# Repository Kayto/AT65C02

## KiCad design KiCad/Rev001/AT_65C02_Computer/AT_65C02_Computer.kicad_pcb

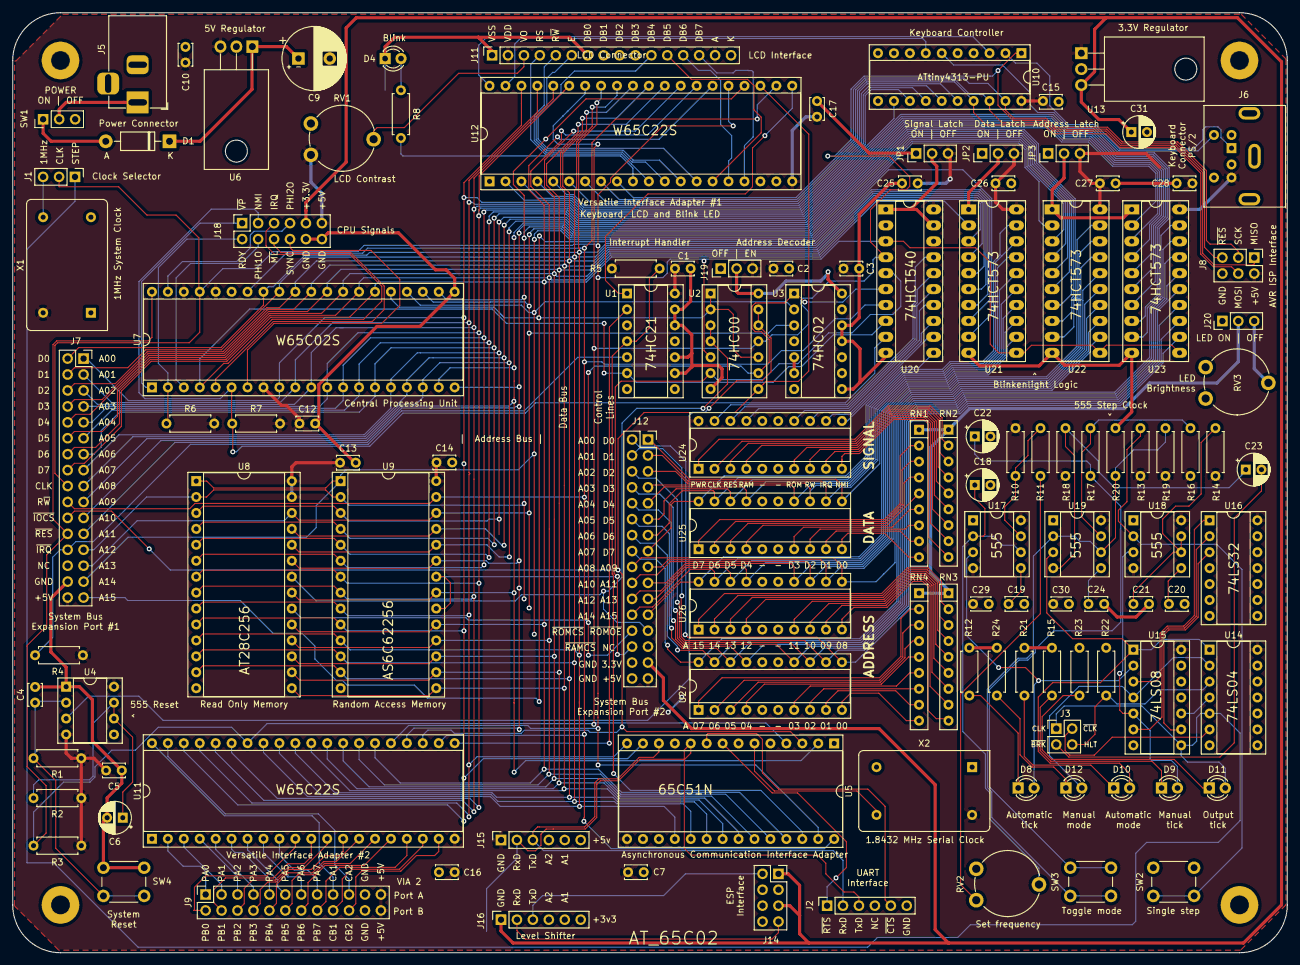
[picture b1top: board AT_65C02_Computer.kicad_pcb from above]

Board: 2 copper layers, 203.2 x 149.9 mm, 122 parts (0 on the bottom side), 200 nets.

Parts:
C1, C2, C3, C4, C5, C7, C10, C12, C13, C14, C15, C16, C17, C19, C20, C21, C24, C25, C26, C27, C28: 0.1uF; C_Disc_D3.4mm_W2.1mm_P2.50mm
C6: 10uF; CP_Radial_D5.0mm_P2.50mm
C9: 1000uF; CP_Radial_D10.0mm_P5.00mm
C18, C22, C23, C31: 1uF; CP_Radial_D5.0mm_P2.50mm
C29: 0.01uF; C_Disc_D3.0mm_W2.0mm_P2.50mm
C30: 0.1uF; C_Disc_D3.0mm_W2.0mm_P2.50mm
D1: 1N5819; D_DO-41_SOD81_P10.16mm_Horizontal
D4: BLINK; LED_D3.0mm
D8: YELLOW_A; LED_D3.0mm
D9: YELLOW_M; LED_D3.0mm
D10: GREEN; LED_D3.0mm
D11: BLUE; LED_D3.0mm
D12: RED; LED_D3.0mm
H1, H2, H3, H4: MountingHole_3mm_Pad
J1: CLK Jumper; PinHeader_1x03_P2.54mm_Vertical
J2: Optional UART Port; PinSocket_1x06_P2.54mm_Vertical
J3: Conn_01x06_Female; PinSocket_2x02_P2.54mm_Vertical
J5: Barrel_Jack-Connector; BarrelJack_Horizontal
J6: Mini-DIN-6; mini_din-6
J7: Expansion port; PinSocket_2x16_P2.54mm_Vertical
J8: AVR-ISP-10; PinHeader_2x03_P2.54mm_Vertical
J9: VIA2PA - VIA2PB; PinSocket_2x12_P2.54mm_Vertical
J11: LCD Connector; PinSocket_1x16_P2.54mm_Vertical
J12: Expansion port #2; PinSocket_2x16_P2.54mm_Vertical
J14: ESP Interface; PinSocket_2x04_P2.54mm_Vertical
J15: Level_Shifter_HV; PinSocket_1x06_P2.54mm_Vertical
J16: Level_Shifter_LV; PinSocket_1x06_P2.54mm_Vertical
J18: CPU Signals; PinSocket_2x06_P2.54mm_Vertical
J19: Address Decoder Enable; PinHeader_1x03_P2.54mm_Vertical
J20: LED SWITCH; PinHeader_1x03_P2.54mm_Vertical
JP1: EN_SIGNAL; PinHeader_1x03_P2.54mm_Vertical
JP2: EN_DATA; PinHeader_1x03_P2.54mm_Vertical
JP3: EN_ADDR; PinHeader_1x03_P2.54mm_Vertical
R1, R14: 1M; R_Axial_DIN0207_L6.3mm_D2.5mm_P7.62mm_Horizontal
R2: 47K; R_Axial_DIN0207_L6.3mm_D2.5mm_P7.62mm_Horizontal
R3: 1k; R_Axial_DIN0207_L6.3mm_D2.5mm_P7.62mm_Horizontal
R4, R5, R6, R7: 4K7; R_Axial_DIN0207_L6.3mm_D2.5mm_P7.62mm_Horizontal
R8: 270; R_Axial_DIN0207_L6.3mm_D2.5mm_P7.62mm_Horizontal
R10, R11, R13, R16, R18, R22: 1K; R_Axial_DIN0207_L6.3mm_D2.5mm_P7.62mm_Horizontal
R12, R15, R21, R23, R24: 220; R_Axial_DIN0207_L6.3mm_D2.5mm_P7.62mm_Horizontal
R17: 100K; R_Axial_DIN0207_L6.3mm_D2.5mm_P7.62mm_Horizontal
R19, R20: 10K; R_Axial_DIN0207_L6.3mm_D2.5mm_P7.62mm_Horizontal
RN1, RN2, RN3, RN4: 330x8; R_Array_SIP9
RV1: 10K; Potentiometer_Piher_PT-10-V10_Vertical
RV2: 1M; Potentiometer_Piher_PT-10-V10_Vertical
RV3: 150k; Potentiometer_Piher_PT-10-V10_Vertical
SW1: SW_SPDT; PinHeader_1x03_P2.54mm_Vertical
SW2: Step; SW_PUSH_6mm
SW3: Mode; SW_PUSH_6mm
SW4: SW_SPDT; SW_PUSH_6mm
U1: 74HC21; DIP-14_W7.62mm_Socket
U2: 74HC00; DIP-14_W7.62mm_Socket
U3: 74HC02; DIP-14_W7.62mm_Socket
U4, U17, U18, U19: NE555; DIP-8_W7.62mm_Socket
U5: 65C51N; DIP-28_W15.24mm_Socket
U6: Regulator_Linear_L7805; TO-220-3_Horizontal_TabDown
U7: 65C02S; DIP-40_W15.24mm_Socket
U8: 28C256; DIP-28_W15.24mm_Socket
U9: 62256; DIP-28_W15.24mm_Socket
U10: ATtiny4313-PU; DIP-20_W7.62mm_Socket
U11, U12: 65C22S; DIP-40_W15.24mm_Socket
U13: L7806; TO-220-3_Horizontal_TabDown
U14: 74LS04; DIP-14_W7.62mm_Socket
U15: 74LS08; DIP-14_W7.62mm_Socket
U16: 74LS32; DIP-14_W7.62mm_Socket
U20: 74HCT540; DIP-20_W7.62mm_Socket_LongPads
U21, U22, U23: 74HCT573; DIP-20_W7.62mm_Socket_LongPads
U24, U25, U26, U27: 10_LED_Array; DIP-20_W7.62mm_Socket
X1: 1MHz; Oscillator_DIP-14
X2: 1.8432MHz; Oscillator_DIP-14

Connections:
+3.3V: C31.1, J12.29, J14.1, J14.5, J16.1, J18.9, U13.3
+5V: C1.1, C2.1, C3.1, C5.1, C7.1, C10.1, C12.1, C13.1, C14.1, C15.1, C16.1, C17.1, C25.1, C26.1, C27.1, C28.1, C29.1, C30.1, J6.4, J7.32, J8.2, J9.23, J9.24, J11.2, J11.15, J12.31, J15.1, J18.11, J19.3, JP1.3, JP2.3, JP3.3, R1.1, R2.1, R3.1, R4.1, R5.1, R6.2, R7.2, R10.1, R13.1, R14.1, R16.1, R18.1, R19.1, RV1.1, U1.14, U4.4, U4.8, U5.15, U6.3, U7.8, U7.36, U7.38, U8.27, U8.28, U9.28, U10.20, U11.20, U12.20, U13.1, U14.14, U15.14, U16.14, U17.4, U17.8, U18.4, U18.8, U19.8, U20.20, U21.20, U22.20, U23.20, U24.20, X1.14, X2.14
/6502 Peripherals/v1pa0: U10.12, U12.2
/6502 Peripherals/v1pa1: U10.13, U12.3
/6502 Peripherals/v1pa2: U10.14, U12.4
/6502 Peripherals/v1pa3: U10.15, U12.5
/6502 Peripherals/v1pa4: U10.16, U12.6
/6502 Peripherals/v1pa5: J8.4, U10.17, U12.7
/6502 Peripherals/v1pa6: J8.1, U10.18, U12.8
/6502 Peripherals/v1pa7: J8.3, U10.19, U12.9
/6502 Peripherals/v1pa8: U10.3, U12.40
/6502 Peripherals/v1pa9: U10.7, U12.39
/6502 Peripherals/v1pb0: R8.1, U12.10
/6502 Peripherals/v1pb1: J11.4, U12.11
/6502 Peripherals/v1pb2: J11.5, U12.12
/6502 Peripherals/v1pb3: J11.6, U12.13
/6502 Peripherals/v1pb4: J11.11, U12.14
/6502 Peripherals/v1pb5: J11.12, U12.15
/6502 Peripherals/v1pb6: J11.13, U12.16
/6502 Peripherals/v1pb7: J11.14, U12.17
/6502 Peripherals/v2pa0: J9.1, U11.2
/6502 Peripherals/v2pa1: J9.3, U11.3
/6502 Peripherals/v2pa2: J9.5, U11.4
/6502 Peripherals/v2pa3: J9.7, U11.5
/6502 Peripherals/v2pa4: J9.9, U11.6
/6502 Peripherals/v2pa5: J9.11, U11.7
/6502 Peripherals/v2pa6: J9.13, U11.8
/6502 Peripherals/v2pa7: J9.15, U11.9
/6502 Peripherals/v2pa8: J9.17, U11.40
/6502 Peripherals/v2pa9: J9.19, U11.39
/6502 Peripherals/v2pb0: J9.2, U11.10
/6502 Peripherals/v2pb1: J9.4, U11.11
/6502 Peripherals/v2pb2: J9.6, U11.12
/6502 Peripherals/v2pb3: J9.8, U11.13
/6502 Peripherals/v2pb4: J9.10, U11.14
/6502 Peripherals/v2pb5: J9.12, U11.15
/6502 Peripherals/v2pb6: J9.14, U11.16
/6502 Peripherals/v2pb7: J9.16, U11.17
/6502 Peripherals/v2pb8: J9.18, U11.18
/6502 Peripherals/v2pb9: J9.20, U11.19
AD_EN: J19.2, U2.14, U3.14
AUTO: D8.2, U15.2, U17.3
CLK: J1.2, J7.18, U2.5, U5.27, U7.37, U11.25, U12.25, U20.3, U21.11, U22.11, U23.11
CLKOUT: J1.3, X1.8
CLKx: D11.2, J1.1, J3.1, U14.5, U15.8
GND: C1.2, C2.2, C3.2, C4.2, C5.2, C6.2, C7.2, C9.2, C10.2, C12.2, C13.2, C14.2, C15.2, C16.2, C17.2, C18.2, C19.2, C20.2, C21.2, C22.2, C24.2, C25.2, C26.2, C27.2, C28.2, C29.2, C30.2, D4.1, J2.6, J5.2, J6.3, J7.30, J8.6, J9.21, J9.22, J11.1, J11.7, J11.8, J11.9, J11.10, J11.16, J12.30, J12.32, J14.8, J15.6, J16.6, J18.10, J18.12, J19.1, JP1.1, JP2.1, JP3.1, R12.2, R15.2, R20.2, R21.2, R22.2, R23.2, R24.2, RV1.3, RV3.3, SW2.1, SW4.1, U1.7, U1.9, U1.10, U1.12, U1.13, U2.7, U3.5, U3.6, U3.7, U3.8, U3.9, U3.11, U3.12, U4.1, U5.1, U5.16, U5.17, U6.2, U7.21, U8.14, U9.14, U10.10, U11.1, U12.1, U13.2, U14.7, U15.7, U16.7, U17.1, U18.1, U19.1, U20.10, U21.10, U22.10, U23.10, X1.7, X2.7
HLT: J3.4, R22.1, U14.3
KBCLK: J6.5, U10.6
KBDAT: J6.1, U10.2
LED_bright: J20.2, RN1.1, RN2.1, RN3.1, RN4.1
MAN: D9.2, U15.5, U18.3
MODE: D10.2, U14.1, U15.1, U19.3
unnamed: C4.1, R1.2, SW4.2, U4.2
unnamed: C6.1, R2.2, U4.6, U4.7
unnamed: C9.1, D1.1, U6.1
unnamed: C18.1, RV2.2, U17.2, U17.6
unnamed: C19.1, U17.5
unnamed: C20.1, U18.5
unnamed: C21.1, R14.2, U18.6, U18.7
unnamed: C22.1, R17.2, SW3.1
unnamed: C23.1, R18.2, U19.4
unnamed: C24.1, U19.5
unnamed: D1.2, SW1.1
unnamed: D4.2, R8.2
unnamed: D8.1, R12.1
unnamed: D9.1, R15.1
unnamed: D10.1, R21.1
unnamed: D11.1, R23.1
unnamed: D12.1, R24.1
unnamed: J5.1, SW1.2
unnamed: J11.3, RV1.2
unnamed: J20.3, RV3.2
unnamed: JP1.2, U20.1, U20.19
unnamed: JP2.2, U21.1
unnamed: JP3.2, U22.1, U23.1
unnamed: R10.2, R11.1, U17.7
unnamed: R11.2, RV2.1
unnamed: R13.2, SW2.2, U18.2
unnamed: R16.2, R17.1, U19.7
unnamed: R19.2, R20.1, SW3.2, U19.2, U19.6
unnamed: RN1.2, U25.1
unnamed: RN1.3, U25.2
unnamed: RN1.4, U25.3
unnamed: RN1.5, U25.4
unnamed: RN1.6, U25.7
unnamed: RN1.7, U25.8
unnamed: RN1.8, U25.9
unnamed: RN1.9, U25.10
unnamed: RN2.2, U24.1
unnamed: RN2.3, U24.2
unnamed: RN2.4, U24.3
unnamed: RN2.5, U24.4
unnamed: RN2.6, U24.7
unnamed: RN2.7, U24.8
unnamed: RN2.8, U24.9
unnamed: RN2.9, U24.10
unnamed: RN3.2, U26.1
unnamed: RN3.3, U26.2
unnamed: RN3.4, U26.3
unnamed: RN3.5, U26.4
unnamed: RN3.6, U26.7
unnamed: RN3.7, U26.8
unnamed: RN3.8, U26.9
unnamed: RN3.9, U26.10
unnamed: RN4.2, U27.1
unnamed: RN4.3, U27.2
unnamed: RN4.4, U27.3
unnamed: RN4.5, U27.4
unnamed: RN4.6, U27.7
unnamed: RN4.7, U27.8
unnamed: RN4.8, U27.9
unnamed: RN4.9, U27.10
unnamed: U2.12, U2.13, U4.3
unnamed: U14.4, U15.10
unnamed: U15.3, U16.1
unnamed: U15.6, U16.2
unnamed: U15.9, U16.3
unnamed: U20.11, U24.11
unnamed: U20.12, U24.12
unnamed: U20.13, U24.13
unnamed: U20.14, U24.14
unnamed: U20.15, U24.17
unnamed: U20.16, U24.18
unnamed: U20.17, U24.19
PHI1O: J18.4, U7.3
PHI2O: J18.7, U7.39
RDY: J18.2, R6.1, U7.2
RS232CLK: U5.6, X2.8
RxD: J2.2, J15.3, U5.12
RxD3: J14.2, J16.3
R~W: J7.20, U5.28, U7.34, U9.27, U11.22, U12.22, U20.7
SYNC: J18.8, U7.7
TxD: J2.3, J15.2, U5.10
TxD3: J14.7, J16.2
a0: J7.1, U5.13, U7.9, U8.10, U9.10, U11.38, U12.38, U23.9
a1: J7.3, U5.14, U7.10, U8.9, U9.9, U11.37, U12.37, U23.8
a2: J7.5, U7.11, U8.8, U9.8, U11.36, U12.36, U23.7
a3: J7.7, U7.12, U8.7, U9.7, U11.35, U12.35, U23.6
a4: J7.9, U7.13, U8.6, U9.6, U23.5
a5: J7.11, U7.14, U8.5, U9.5, U23.4
a6: J7.13, U7.15, U8.4, U9.4, U23.3
a7: J7.15, U7.16, U8.3, U9.3, U23.2
a8: J7.17, U7.17, U8.25, U9.25, U22.9
a9: J7.19, U7.18, U8.24, U9.24, U22.8
a10: J7.21, U5.2, U7.19, U8.21, U9.21, U22.7
a11: J7.23, U7.20, U8.23, U9.23, U11.24, U22.6
a12: J7.25, U7.22, U8.2, U9.2, U12.24, U22.5
a13: J7.27, U3.3, U7.23, U8.26, U9.26, U22.4
a14: J7.29, U3.2, U7.24, U8.1, U9.1, U22.3
a15: J7.31, U2.1, U2.2, U2.10, U7.25, U22.2
ab0: J12.2, U23.12, U27.11
ab1: J12.4, U23.13, U27.12
ab2: J12.6, U23.14, U27.13
ab3: J12.8, U23.15, U27.14
ab4: J12.10, U23.16, U27.17
ab5: J12.12, U23.17, U27.18
ab6: J12.14, U23.18, U27.19
ab7: J12.16, U23.19, U27.20
ab8: J12.18, U22.12, U26.11
ab9: J12.17, U22.13, U26.12
ab10: J12.20, U22.14, U26.13
ab11: J12.19, U22.15, U26.14
ab12: J12.22, U22.16, U26.17
ab13: J12.21, U22.17, U26.18
ab14: J12.24, U22.18, U26.19
ab15: J12.23, U22.19, U26.20
d0: J7.2, U5.18, U7.33, U8.11, U9.11, U11.33, U12.33, U21.9
d1: J7.4, U5.19, U7.32, U8.12, U9.12, U11.32, U12.32, U21.8
d2: J7.6, U5.20, U7.31, U8.13, U9.13, U11.31, U12.31, U21.7
d3: J7.8, U5.21, U7.30, U8.15, U9.15, U11.30, U12.30, U21.6
d4: J7.10, U5.22, U7.29, U8.16, U9.16, U11.29, U12.29, U21.5
d5: J7.12, U5.23, U7.28, U8.17, U9.17, U11.28, U12.28, U21.4
d6: J7.14, U5.24, U7.27, U8.18, U9.18, U11.27, U12.27, U21.3
d7: J7.16, U5.25, U7.26, U8.19, U9.19, U11.26, U12.26, U21.2
db0: J12.1, U21.12, U25.11
db1: J12.3, U21.13, U25.12
db2: J12.5, U21.14, U25.13
db3: J12.7, U21.15, U25.14
db4: J12.9, U21.16, U25.17
db5: J12.11, U21.17, U25.18
db6: J12.13, U21.18, U25.19
db7: J12.15, U21.19, U25.20
~AIRQ: R5.2, U1.4, U5.26
~BRK: C23.2, J3.2
~CLKx: J3.3, U14.6
~CTS: J2.5, U5.9
~IOCS: J7.22, U2.8, U5.3, U11.23, U12.23
~IRQ: J18.5, U1.6, U7.4, U20.8
~IRQX: J7.26, R4.2, U1.5
~ML: J18.6, U7.5
~MODE: D12.2, U14.2, U15.4
~NMI: J18.3, R7.1, U7.6, U20.9
~RAM_CS: J12.28, U2.6, U9.20, U9.22, U20.5
~RES: J7.24, J8.5, R3.2, U2.11, U5.4, U7.40, U10.1, U11.34, U12.34, U20.4
~ROM_CS: J12.26, U2.9, U3.1, U8.20, U20.6
~ROM_OE: J12.25, U2.3, U2.4, U8.22
~RTS: J2.1, U5.8
~V1IRQ: U1.1, U12.21
~V2IRQ: U1.2, U11.21
~VP: J18.1, U7.1
